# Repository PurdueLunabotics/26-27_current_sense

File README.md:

# Current sense board

This is a repo that will contain the current sense board(s?) for the team.

If/when you make multiple PCBs, let me (Alex) know and I can set this repo up for that. It'll involve moving projects into subfolders and updating the image generation script, but that's not very hard.

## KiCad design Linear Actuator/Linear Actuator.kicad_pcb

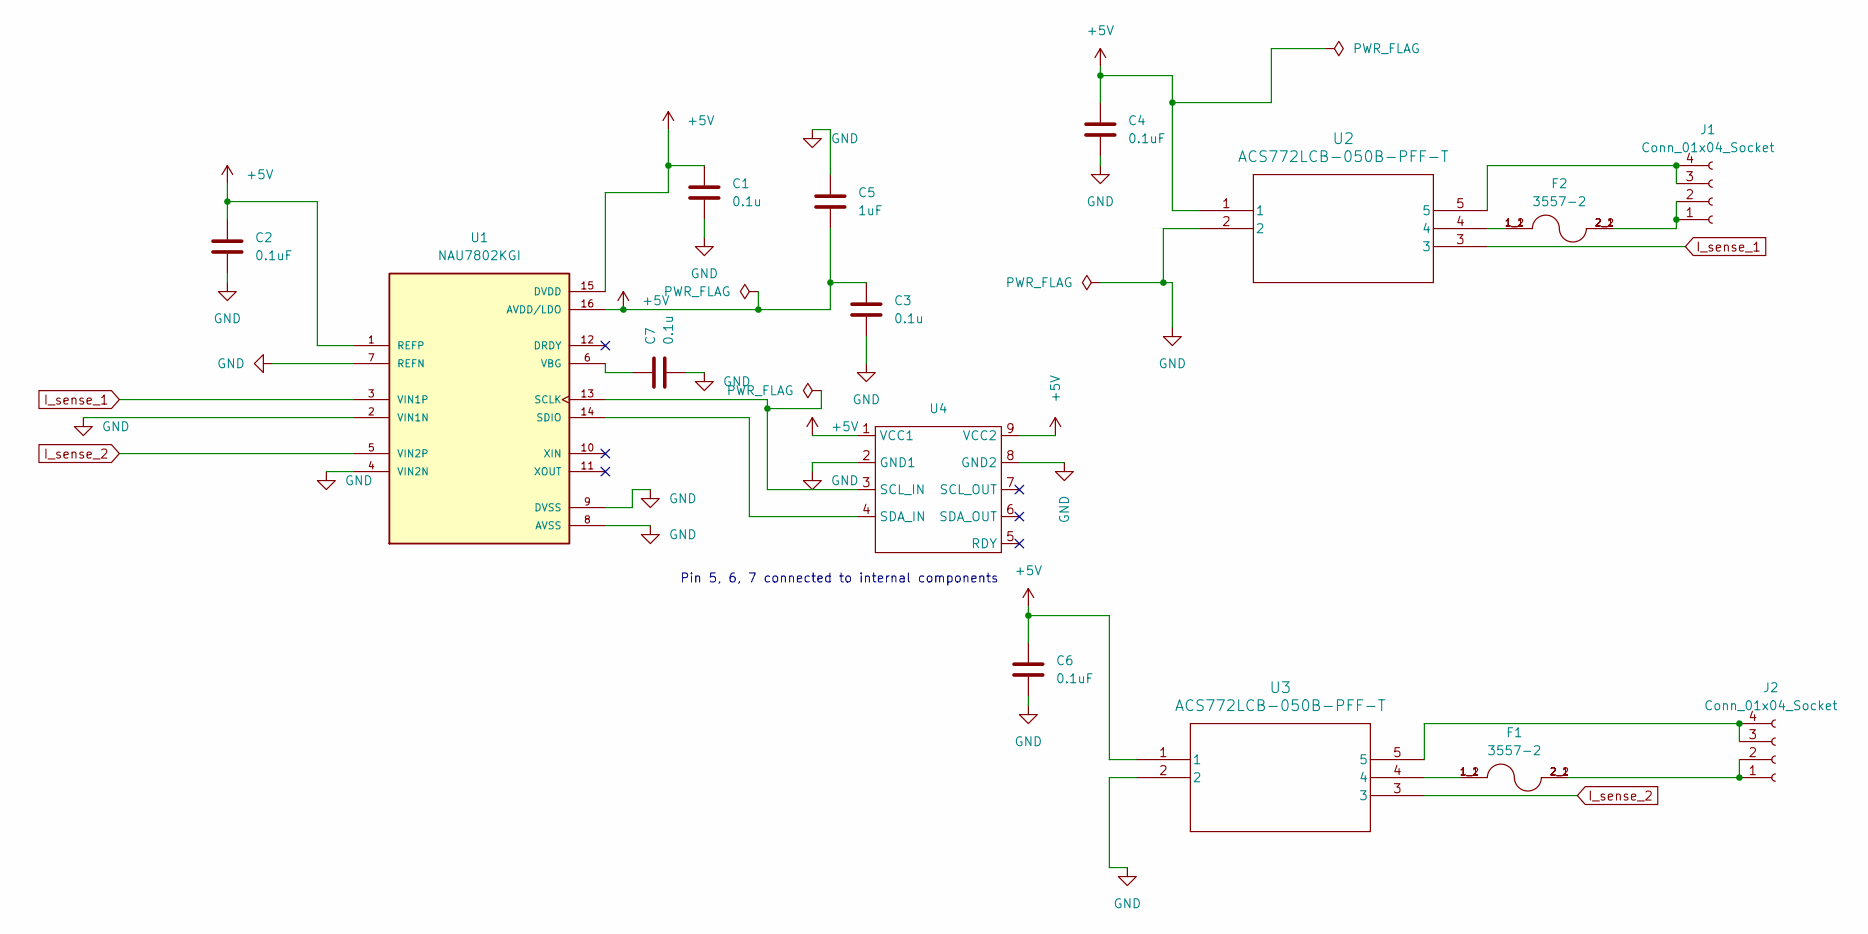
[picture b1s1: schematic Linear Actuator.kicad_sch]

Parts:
C1, C3, C7: 0.1u; C_Disc_D4.7mm_W2.5mm_P5.00mm
C2, C4, C6: 0.1uF; C_Disc_D4.7mm_W2.5mm_P5.00mm
C5: 1uF; C_Disc_D4.7mm_W2.5mm_P5.00mm
F1, F2: 3557-2; FUSE_3557-2; PARTREV D
J1, J2: Conn_01x04_Socket; CONN2_2604-1102_WAG
U1: NAU7802KGI; DIP792W45P254L1904H533Q16; PARTREV 2.6; DigiKey_Part_Number NAU7802KGI-ND
U2, U3: ACS772LCB-050B-PFF-T; XDCR_ACS772LCB-050B-PFF-T
U4: DFR1193

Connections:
+5V: C1.1, C2.1, C3.1, C4.1, C5.2, C6.1, U1.1 (REFP), U1.15 (DVDD), U1.16 (AVDD/LDO), U2.1, U3.1, U4.1 (VCC1), U4.9 (VCC2)
GND: C1.2, C2.2, C3.2, C4.2, C5.1, C6.2, C7.2, U1.2 (VIN1N), U1.4 (VIN2N), U1.7 (REFN), U1.8 (AVSS), U1.9 (DVSS), U2.2, U3.2, U4.2 (GND1), U4.8 (GND2)
I_sense_1: U1.3 (VIN1P), U2.3
I_sense_2: U1.5 (VIN2P), U3.3
unnamed: F1.1_1, F1.1_2, U3.4
unnamed: F2.1_1, F2.1_2, U2.4
unnamed: F2.2_1, F2.2_2, J1.1, J1.2
unnamed: J1.3, J1.4, U2.5
unnamed: F1.2_1, F1.2_2, J2.1, J2.2
unnamed: J2.3, J2.4, U3.5
unnamed: U1.13 (SCLK), U4.3 (SCL_IN)
unnamed: U1.14 (SDIO), U4.4 (SDA_IN)
unnamed: C7.1, U1.6 (VBG)

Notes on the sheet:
Pin 5, 6, 7 connected to internal components

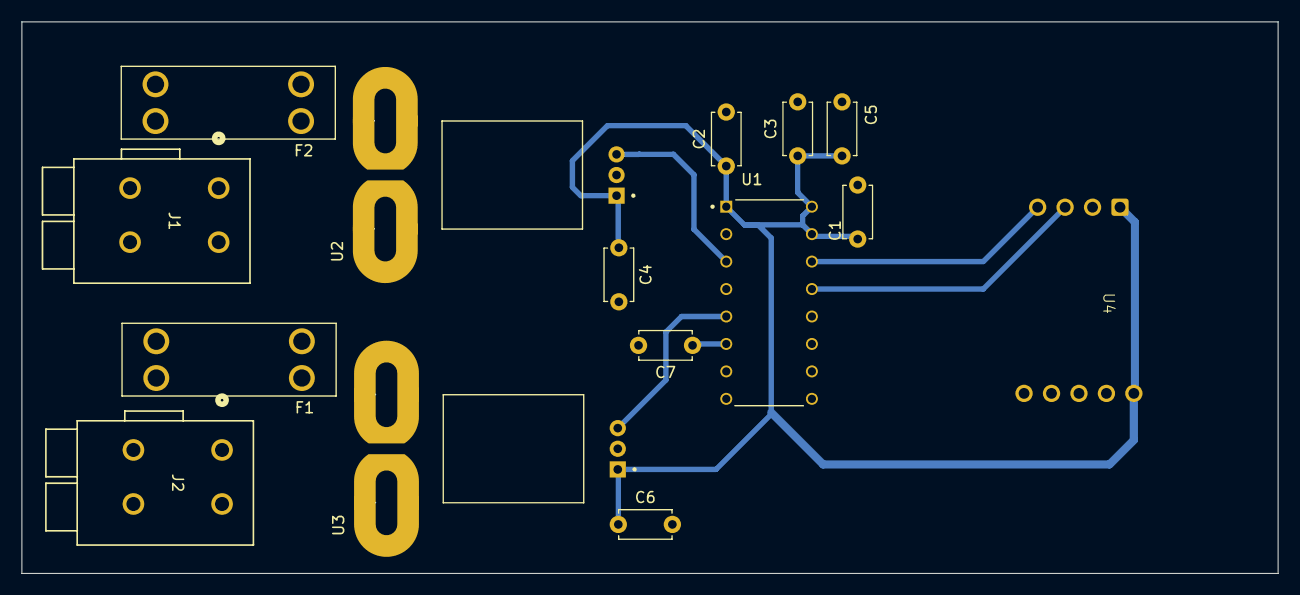
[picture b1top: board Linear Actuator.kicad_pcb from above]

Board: 2 copper layers, 116.2 x 51.0 mm, 15 parts (0 on the bottom side), 13 nets.

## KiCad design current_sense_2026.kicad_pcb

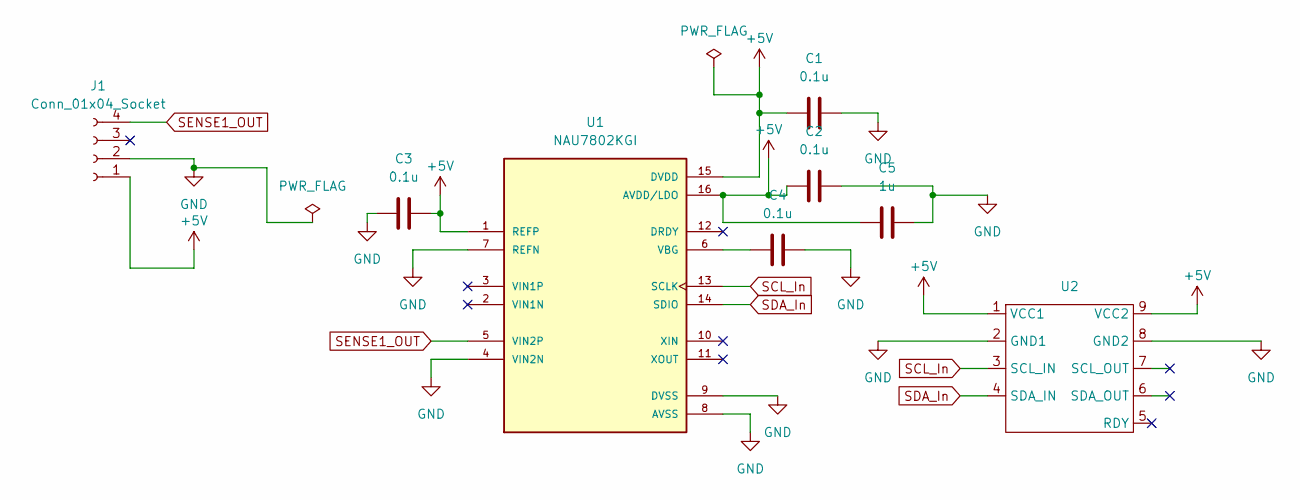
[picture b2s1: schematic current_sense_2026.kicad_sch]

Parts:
C1, C2, C3, C4: 0.1u; C_Disc_D4.7mm_W2.5mm_P5.00mm
C5: 1u; C_Disc_D4.7mm_W2.5mm_P5.00mm
J1: Conn_01x04_Socket; JST_XH_B4B-XH-A_1x04_P2.50mm_Vertical
U1: NAU7802KGI; DIP-16_W7.62mm_LongPads; PARTREV 2.6
U2: DFR1193

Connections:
+5V: C1.1, C2.1, C3.2, C5.1, J1.1, U1.1 (REFP), U1.15 (DVDD), U1.16 (AVDD/LDO), U2.1 (VCC1), U2.9 (VCC2)
GND: C1.2, C2.2, C3.1, C4.2, C5.2, J1.2, U1.4 (VIN2N), U1.7 (REFN), U1.8 (AVSS), U1.9 (DVSS), U2.2 (GND1), U2.8 (GND2)
unnamed: C4.1, U1.6 (VBG)
SCL_In: U1.13 (SCLK), U2.3 (SCL_IN)
SDA_In: U1.14 (SDIO), U2.4 (SDA_IN)
SENSE1_OUT: J1.4, U1.5 (VIN2P)

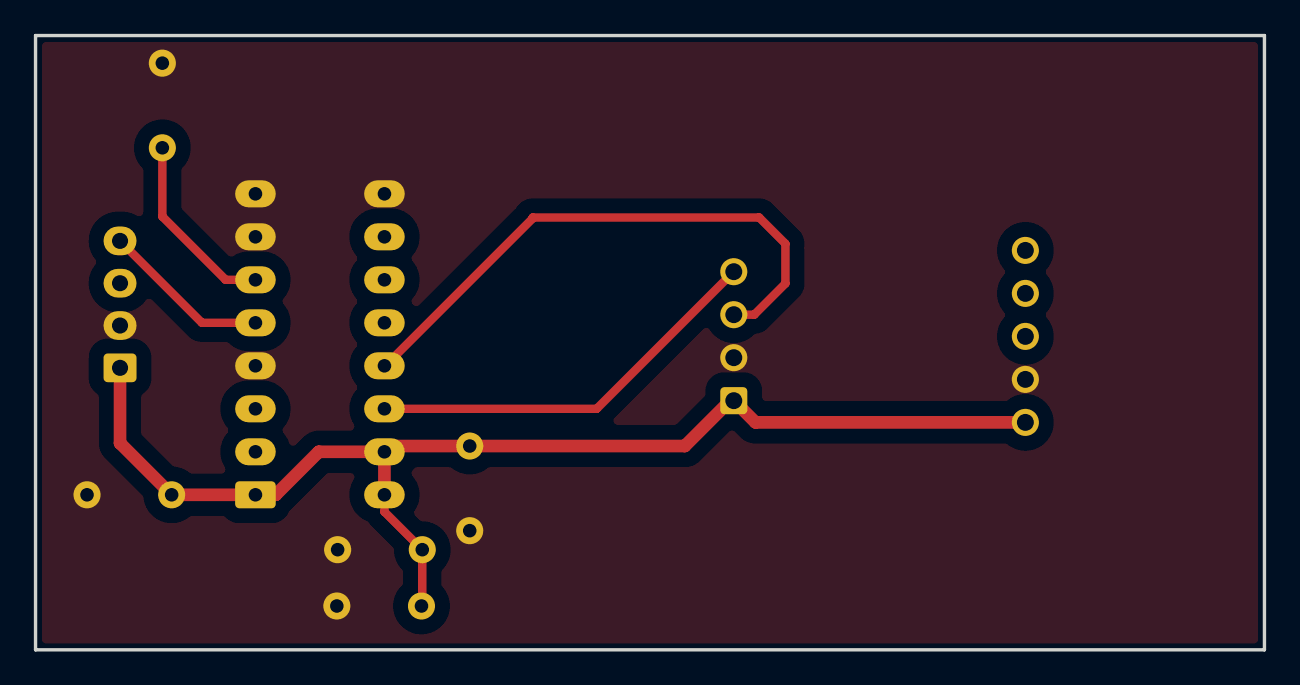
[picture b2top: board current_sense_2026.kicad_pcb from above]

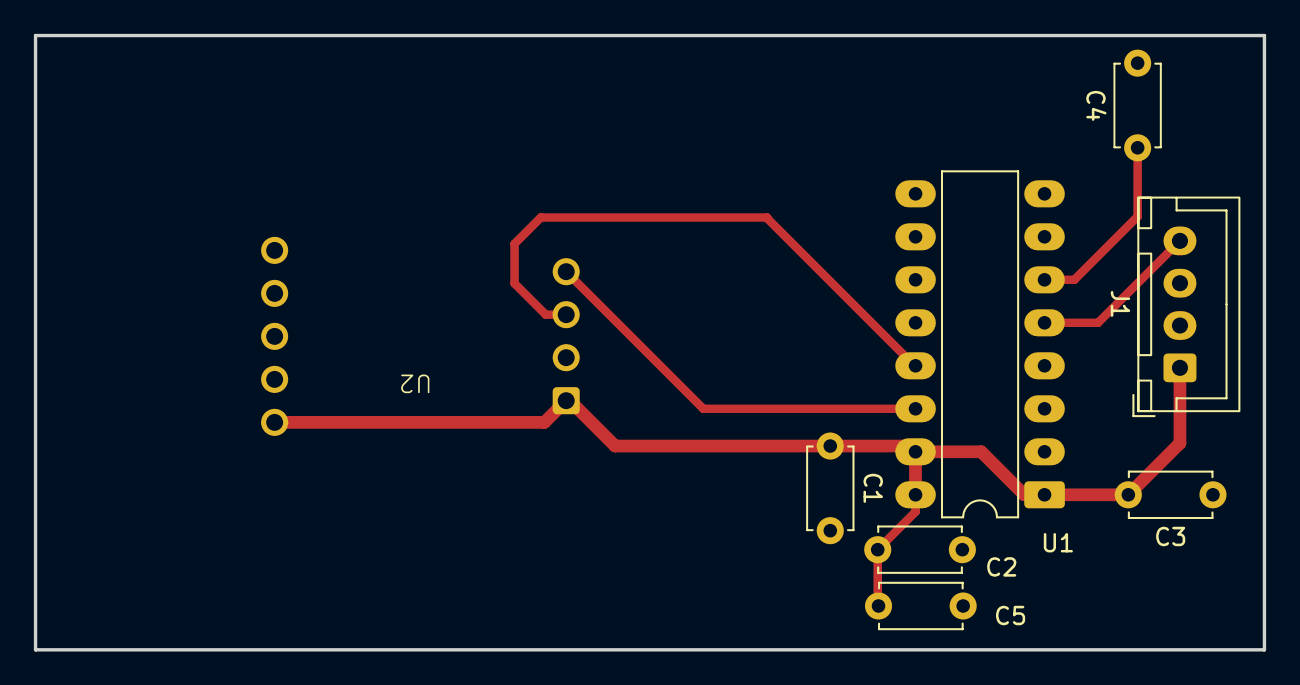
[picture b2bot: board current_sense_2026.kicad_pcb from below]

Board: 2 copper layers, 72.6 x 36.3 mm, 8 parts (8 on the bottom side), 6 nets.
